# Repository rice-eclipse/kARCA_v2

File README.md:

# kARCA 2.0
kARCA 2.0 is a revision of [kARCA](https://github.com/rice-eclipse/karca):  Rice Eclipse's Engine Control System PCB for the data collection and remote control 
of their Titan II and Proxima Hybrid Rocket Motors

It performs the same functions as kARCA with the addition of thermocouple data collection, driver current monitoring, and battery monitoring.
In addition, various components have been replaced for updated ICs and the power regulation and load cell circuits have been revised.

A detailed description of the changes can be found on  [karca_v2/Docs/changelog](https://github.com/rice-eclipse/kARCA_v2/blob/main/karca_v2/Docs/kARCA_v2_Changelog.csv)

Detailed documentation on the circuit board can be found on [karca_v2/Docs/main_documentation](https://github.com/rice-eclipse/kARCA_v2/tree/main/karca_v2/Docs/karca_v2.md)

## Download and Usage
Download [KiCAD](https://www.kicad.org/download/)

Navigate to your preferred folder and clone into the repository:
```
git clone https://github.com/rice-eclipse/kARCA_v2.git
```
Open KiCAD and open the project file (.kicad_pro):
```
File > Open Project
```

Schematics: [karca_v2/Docs/Schematics](https://github.com/rice-eclipse/kARCA_v2/tree/main/karca_v2/Docs/Schematics)

Spice Simulations: [karca_v2/Docs/Simulations](https://github.com/rice-eclipse/kARCA_v2/tree/main/karca_v2/Docs/Simulations)

Board Files: [karca_v2/Docs/Board_Files](https://github.com/rice-eclipse/kARCA_v2/tree/main/karca_v2/Docs/Board_Files)

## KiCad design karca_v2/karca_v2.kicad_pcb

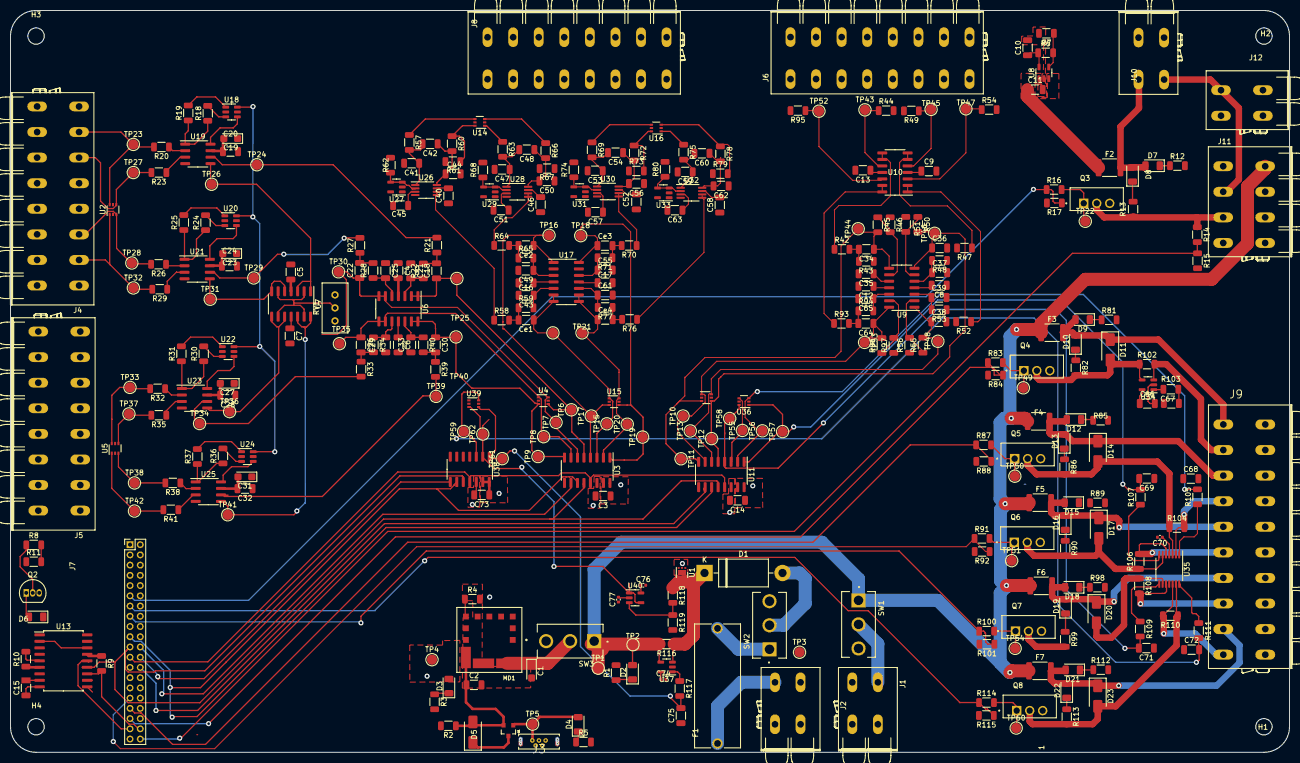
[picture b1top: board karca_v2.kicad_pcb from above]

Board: 4 copper layers, 250.0 x 145.0 mm, 361 parts (0 on the bottom side), 199 nets.

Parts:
C1, C19, C23, C27, C31: 10u; CP_EIA-3216-18_Kemet-A
C2, C10, C11: 10u; C_1206_3216Metric
C3, C4, C5, C6, C7, C16, C17, C20, C24, C28, C32, C40, C42, C45, C46, C48, C51, C52, C54, C57, C58, C60, C63, C66, C67, C68, C69, C71, C72, C73, C75: 0.1u; C_1206_3216Metric
C8, C9, C12, C13, C14: 100n; C_1206_3216Metric
C15: 1u; C_1206_3216Metric
C18, C22, C26, C30, C34, C36, C38, C64: 0.15u; C_1206_3216Metric
C21, C25, C29, C33, C35, C37, C39, C43, C49, C55, C61, C65: 0.075u; C_1206_3216Metric
C41, C44, C47, C50, C53, C56, C59, C62: 0.01u; C_1206_3216Metric
C70, C74, C76, C77: 0.1u; C_0402_1005Metric
Ce1, Ce2, Ce3, Ce4: 0.15u; C_1206_3216Metric
D1: 1N5822RLG; D_DO-201AD_P15.24mm_Horizontal
D2, D3, D4, D7, D8, D9, D10, D12, D13, D15, D16, D18, D19, D21, D22: LED; LED_1206_3216Metric
D5, D11, D14, D17, D20, D23: D_Schottky; D_SMA
D6: HBT; LED_1206_3216Metric
F1: 10A; FUSE_4628
F2, F3, F4, F5, F6, F7: Fuse; Fuse_1812_4532Metric
H1, H2, H3, H4: MountingHole; MountingHole_3.2mm_M3
J1: CON_FAN1; P-2604-1102
J2: Conn_Batt; P-2604-1102
J3: USB_B_Micro; GCT_USB3130-XX-X_REVD
J4: LoadCell_1_2; P-2604-1108
J5: LoadCell_3_4; P-2604-1108
J6, J8: Screw_Terminal_01x08; P-2604-1108
J7: Raspberry_pi; PinHeader_2x20_P2.00mm_Vertical
J9: Screw_Terminal_01x10; P-2604-1110
J10: Keyhole ignition switch; P-2604-1102
J11: Screw_Terminal_01x04; P-2604-1104
J12: Buzzer; P-2604-1102
MD1: OKL-T_6-W12N-C; MURATA_OKL-T-6-W12N-C_0
Q1: AO3401A; SOT23-3
Q2: PN2222A; TO-92_Inline
Q3, Q4, Q5, Q6, Q7, Q8: IRF3708; TO254P1041X444X1930-3
R1: 470; R_1206_3216Metric
R2, R9, R10, R11, R17, R84, R88, R92, R101, R115: 10k; R_1206_3216Metric
R3, R5: 250; R_1206_3216Metric
R4: 1.34k; R_1206_3216Metric
R6: 10.4M; R_1206_3216Metric
R7: 1.2M; R_1206_3216Metric
R8, R12, R13, R16, R20, R21, R22, R23, R26, R27, R28, R29, R32, R33, R34, R35, R38, R39, R40, R41, R42, R43, R47, R48, R52, R53, R58, R59, R62, R64, R65, R68, R70, R71, R74, R76, R77, R80, R81, R82, R83, R85, R86, R87, R89, R90, R91, R93, R94, R98, R99, R100, R103, R105, R107, R109, R111, R112, R113, R114, R117: 1k; R_1206_3216Metric
R14: 15k; R_1206_3216Metric
R15: 5k; R_1206_3216Metric
R18, R24, R30, R36: 330; R_1206_3216Metric
R19, R25, R31, R37, R46, R51, R56, R97: 6.7k; R_1206_3216Metric
R44, R49, R54, R95: 30; R_1206_3216Metric
R45, R50, R55, R96: 47k; R_1206_3216Metric
R57, R60, R63, R66, R69, R72, R75, R78: 100; R_1206_3216Metric
R61, R67, R73, R79: 1M; R_1206_3216Metric
R102, R104, R106, R108, R110, R116: 10m; R_1206_3216Metric
R118: 100k; R_1206_3216Metric
R119: 50k; R_1206_3216Metric
RV1: 30k; Potentiometer_Bourns_3296W_Vertical
SW1, SW2, SW3: SW_SPST; SW_500SSP1S2M2QEA
TP1, TP2, TP3, TP4, TP5, TP6, TP7, TP8, TP9, TP10, TP11, TP12, TP13, TP14, TP15, TP16, TP17, TP18, TP19, TP20, TP21, TP22, TP23, TP24, TP25, TP26, TP27, TP28, TP29, TP30, TP31, TP32, TP33, TP34, TP35, TP36, TP37, TP38, TP39, TP40, TP41, TP42, TP43, TP44, TP45, TP46, TP47, TP48, TP49, TP50, TP51, TP52, TP53, TP54, TP55, TP56, TP57, TP58, TP59, TP60, TP61, TP62: TestPoint; TestPoint_Pad_D2.0mm
U1: TVS1400DRV; WSON-6-1EP_2x2mm_P0.65mm_EP1x1.6mm
U2, U4, U5, U12, U14, U15, U16, U36, U39: NUP4202; SOT-363_SC-70-6
U3, U11: MCP3208; SOIC-16_3.9x9.9mm_P1.27mm
U6, U7, U9, U10, U17: TLV9304xD; SO-14_3.9x8.65mm_P1.27mm
U8: TPS7A24; SOT-23-5
U13: M41T93; SOIC-18W_7.5x11.6mm_P1.27mm
U18, U20, U22, U24: TS5A3159ADBVR; SOT-23-6
U19, U21, U23, U25: AD8223; SOIC-8_3.9x4.9mm_P1.27mm
U26, U28, U30, U32: AD8495; MSOP-8_3x3mm_P0.65mm
U27, U29, U31, U33: SOT-23-5
U34: INA180A4; SOT-23-5
U35: TSSOP-14_4.4x5mm_P0.65mm
U37: INA180A2; SOT-23-5
U38: MCP3204; SO-14_3.9x8.65mm_P1.27mm
U40: TLV9301xDBV; SOT-23-5

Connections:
+5V: C2.1, C3.1, C4.2, C5.2, C8.2, C9.1, C14.1, C16.2, C19.2, C20.2, C23.2, C24.2, C27.2, C28.2, C31.2, C32.2, C40.2, C46.2, C52.2, C58.2, C66.1, C70.1, C73.1, C74.1, C76.1, D3.2 (A), D5.1 (K), D5.2 (A), J4.1, J4.5, J7.2, J7.4, MD1.4 (VOUT), Q1.2 (G), Q1.3 (S), Q2.3 (C), R2.1, R9.1, R10.1, R62.2, R68.2, R74.2, R80.2, RV1.3, TP4.1, U2.5, U3.15 (Vref), U3.16 (Vdd), U4.5, U5.5, U6.4 (V+), U7.4 (V+), U9.4 (V+), U10.4 (V+), U11.15 (Vref), U11.16 (Vdd), U12.5, U13.6 (DU), U13.15 (VCC), U14.5, U15.5, U16.5, U17.4 (V+), U18.5 (V+), U19.7 (Vs+), U20.5 (V+), U21.7 (Vs+), U22.5 (V+), U23.7 (Vs+), U24.5 (V+), U25.7 (Vs+), U26.7 (+Vs), U28.7 (+Vs), U30.7 (+Vs), U32.7 (+Vs), U34.5 (V+), U35.4 (VS), U36.5, U37.5 (V+), U38.13 (Vref), U38.14 (Vdd), U39.5, U40.5 (V+)
+12V: C11.1, D2.2 (A), F2.1, F3.1, F4.1, F5.1, F6.1, F7.1, J11.1, R116.2, SW1.1 (A), SW3.1 (A), TP1.1, TP2.1, U8.1 (IN), U8.3 (EN), U37.4 (-)
/DRV1_ADC: C67.2, R103.2, TP55.1, U11.3 (CH2), U36.4
/DRV2_ADC: C68.2, R105.2, TP56.1, U11.2 (CH1), U36.3
/DRV3_ADC: C69.2, R107.2, TP57.1, U11.1 (CH0), U36.1
/DRV4_ADC: C71.2, R109.2, TP58.1, U11.4 (CH3), U36.6
/Drivers/DRV1_CTL: J7.35, R83.1, R84.1
/Drivers/DRV1_NEG: J9.2, R102.2, U34.3 (+)
/Drivers/DRV2_CTL: J7.33, R87.1, R88.1
/Drivers/DRV2_NEG: J9.4, R104.2, U35.2 (IN1+)
/Drivers/DRV3_CTL: J7.31, R91.1, R92.1
/Drivers/DRV3_NEG: J9.6, R106.2, U35.5 (IN2+)
/Drivers/DRV4_CTL: J7.15, R100.1, R101.1
/Drivers/DRV4_NEG: J9.8, R108.2, U35.10 (IN3+)
/Drivers/DRV5_ADC: C72.2, R111.2, TP59.1, U38.3 (CH2), U39.6
/Drivers/DRV5_CTL: J7.13, R114.1, R115.1
/Drivers/DRV5_NEG: J9.10, R110.2, U35.12 (IN4+)
/Drivers/IGN_CONT: J7.40, R14.2, R15.1
/Drivers/IGN_CTL: J7.11, R16.1, R17.1
/Drivers/IGN_NEG: J11.3, Q3.2 (D), R13.2, R14.1
/Drivers/IGN_POS: D7.2 (A), D8.2 (A), F2.2, J10.1, J10.2, J11.2, J12.1
/Drivers/MOS1: D11.2 (A), Q4.2 (D), R82.2, R102.1, U34.4 (-)
/Drivers/MOS2: D14.2 (A), Q5.2 (D), R86.2, R104.1, U35.3 (IN1-)
/Drivers/MOS3: D17.2 (A), Q6.2 (D), R90.2, R106.1, U35.6 (IN2-)
/Drivers/MOS4: D20.2 (A), Q7.2 (D), R99.2, R108.1, U35.9 (IN3-)
/Drivers/MOS5: D23.2 (A), Q8.2 (D), R110.1, R113.2, U35.13 (IN4-)
/Drivers/driver_nmos1/DRV_POS: D12.2 (A), D13.2 (A), D14.1 (K), F4.2, J9.3
/Drivers/driver_nmos2/DRV_POS: D15.2 (A), D16.2 (A), D17.1 (K), F5.2, J9.5
/Drivers/driver_nmos3/DRV_POS: D18.2 (A), D19.2 (A), D20.1 (K), F6.2, J9.7
/Drivers/driver_nmos4/DRV_POS: D21.2 (A), D22.2 (A), D23.1 (K), F7.2, J9.9
/Drivers/driver_nmos/DRV_POS: D9.2 (A), D10.2 (A), D11.1 (K), F3.2, J9.1
/Load Cells/IN_AMP_VREF: RV1.2, U7.2 (-), U7.6 (-), U7.9 (-), U7.13 (-)
/Load Cells/LC_Amplification1/IN1: J4.6, R26.2, TP28.1, U2.3
/Load Cells/LC_Amplification1/IN2: J4.7, R29.2, TP32.1, U2.1
/Load Cells/LC_Amplification1/OUT: C22.1, TP7.1, TP30.1, U3.6 (CH5), U4.6, U6.6 (-), U6.7
/Load Cells/LC_Amplification2/IN1: R32.2, TP33.1, U5.6
/Load Cells/LC_Amplification2/IN2: R35.2, TP37.1, U5.4
/Load Cells/LC_Amplification2/OUT: C26.1, TP8.1, TP35.1, U3.7 (CH6), U4.1, U6.8, U6.9 (-)
/Load Cells/LC_Amplification3/IN1: R38.2, TP38.1, U5.3
/Load Cells/LC_Amplification3/IN2: R41.2, TP42.1, U5.1
/Load Cells/LC_Amplification3/OUT: C30.1, TP9.1, TP40.1, U3.8 (CH7), U4.3, U6.13 (-), U6.14
/Load Cells/LC_Amplification/IN1: J4.2, R20.2, TP23.1, U2.6
/Load Cells/LC_Amplification/IN2: J4.3, R23.2, TP27.1, U2.4
/Load Cells/LC_Amplification/OUT: C18.1, TP6.1, TP25.1, U3.5 (CH4), U4.4, U6.1, U6.2 (-)
/Load Cells/LC_CS: J7.22, U3.10 (~CS/SHDN)
/Load Cells/LC_SELECTOR: J7.16, U18.6, U20.6, U22.6, U24.6
/Load Cells/TC_1_ADC: Ce1.1, TP14.1, TP15.1, U3.3 (CH2), U15.1, U17.6 (-), U17.7
/Load Cells/TC_2_ADC: Ce2.1, TP16.1, TP17.1, U3.4 (CH3), U15.3, U17.1, U17.2 (-)
/Load Cells/TC_3_ADC: Ce3.1, TP18.1, TP19.1, U3.1 (CH0), U15.4, U17.13 (-), U17.14
/Load Cells/TC_4_ADC: Ce4.1, TP20.1, TP21.1, U3.2 (CH1), U15.6, U17.8, U17.9 (-)
/Pressure Transducers/CS: J7.26, U11.10 (~CS/SHDN)
/Pressure Transducers/pt_circuitry1/IN: R44.1, TP43.1, U10.10 (+)
/Pressure Transducers/pt_circuitry1/OUT: C34.1, R45.2, TP11.1, TP44.1, U9.8, U11.8 (CH7), U12.3
/Pressure Transducers/pt_circuitry2/IN: R49.1, TP45.1, U10.5 (+)
/Pressure Transducers/pt_circuitry2/OUT: C36.1, R50.2, TP12.1, TP46.1, U9.7, U11.5 (CH4), U12.4
/Pressure Transducers/pt_circuitry3/IN: R54.1, TP47.1, U10.3 (+)
/Pressure Transducers/pt_circuitry3/OUT: C38.1, R55.2, TP13.1, TP48.1, U9.1, U11.6 (CH5), U12.6
/Pressure Transducers/pt_circuitry/IN: R95.1, TP52.1, U10.12 (+)
/Pressure Transducers/pt_circuitry/OUT: C64.1, R96.2, TP10.1, TP53.1, U9.14, U11.7 (CH6), U12.1
/Raspberry Pi/ADC2_CS: J7.24, U38.8 (~CS/SHDN)
/Raspberry Pi/RTC_CS: J7.37, U13.14 (E)
/Raspberry Pi/RTC_IRQ: J7.38, R9.2, U13.12 (IRQ)
/Regulators/battery_monitoring/Battery+: D1.1 (K), R116.1, R118.1, U1.4 (IN), U1.5 (IN), U1.6 (IN), U37.3 (+)
/SPI.CLK: J7.23, U3.13 (CLK), U11.13 (CLK), U13.11 (SCL), U38.11 (CLK)
/SPI.MISO: J7.21, U3.12 (Dout), U11.12 (Dout), U13.13 (SDO), U38.10 (Dout)
/SPI.MOSI: J7.19, U3.11 (Din), U11.11 (Din), U13.10 (SDI), U38.9 (Din)
/thermocouples/thermocouple_amp1/IN_1: R63.1, U14.1
/thermocouples/thermocouple_amp1/IN_2: R66.1, R67.2, U14.3
/thermocouples/thermocouple_amp2/IN_1: R69.1, U16.4
/thermocouples/thermocouple_amp2/IN_2: R72.1, R73.2, U16.6
/thermocouples/thermocouple_amp3/IN_1: R75.1, U16.1
/thermocouples/thermocouple_amp3/IN_2: R78.1, R79.2, U16.3
/thermocouples/thermocouple_amp/IN_1: R57.1, U14.4
/thermocouples/thermocouple_amp/IN_2: R60.1, R61.2, U14.6
GND: C1.2, C2.2, C3.2, C4.1, C5.1, C6.1, C6.2, C7.1, C7.2, C8.1, C9.2, C10.2, C11.2, C12.1, C12.2, C13.1, C13.2, C14.2, C15.1, C16.1, C17.1, C17.2, C19.1, C20.1, C21.1, C23.1, C24.1, C25.1, C27.1, C28.1, C29.1, C31.1, C32.1, C33.1, C35.2, C37.2, C39.2, C40.1, C41.2, C43.2, C44.1, C45.1, C45.2, C46.1, C47.2, C49.2, C50.1, C51.1, C51.2, C52.1, C53.2, C55.2, C56.1, C57.1, C57.2, C58.1, C59.2, C61.2, C62.1, C63.1, C63.2, C65.2, C66.2, C67.1, C68.1, C69.1, C70.2, C71.1, C72.1, C73.2, C74.2, C75.1, C76.2, C77.1, C77.2, D6.1 (K), J1.2, J2.1, J3.5 (GND), J3.6 (Shield), J4.4, J4.8, J7.6, J7.9, J7.14, J7.25, J7.30, J7.34, J7.39, J11.4, J12.2, MD1.3 (1_GROUND), MD1.7 (2_GROUND), Q3.3 (S), Q4.3 (S), Q5.3 (S), Q6.3 (S), Q7.3 (S), Q8.3 (S), R1.2, R2.2, R3.2, R4.2, R5.2, R7.2, R11.1, R12.2, R15.2, R17.2, R44.2, R46.1, R49.2, R51.1, R54.2, R56.1, R61.1, R67.1, R73.1, R79.1, R81.2, R84.2, R85.2, R88.2, R89.2, R92.2, R95.2, R97.1, R98.2, R101.2, R112.2, R115.2, R119.2, RV1.1, TP3.1, U1.1 (GND), U1.2 (GND), U1.3 (GND), U1.7 (GND), U2.2, U3.9 (DGND), U3.14 (AGND), U4.2, U5.2, U6.11 (V-), U7.11 (V-), U8.2 (GND), U9.11 (V-), U10.11 (V-), U11.9 (DGND), U11.14 (AGND), U12.2, U13.2 (NF), U13.9 (VSS), U13.16 (NF), U14.2, U15.2, U16.2, U17.11 (V-), U18.2 (GND), U19.4 (-Vs), U20.2 (GND), U21.4 (-Vs), U22.2 (GND), U23.4 (-Vs), U24.2 (GND), U25.4 (-Vs), U26.3 (-Vs), U27.5 (A), U28.3 (-Vs), U29.5 (A), U30.3 (-Vs), U31.5 (A), U32.3 (-Vs), U33.5 (A), U34.2 (GND), U35.11 (GND), U36.2, U37.2 (GND), U38.7 (DGND), U38.12 (AGND), U39.2, U40.2 (V-)
unnamed: C18.2, R21.1, R22.2
unnamed: C22.2, R27.1, R28.2
unnamed: C26.2, R33.1, R34.2
unnamed: C30.2, R39.1, R40.2
unnamed: C34.2, R42.2, R43.1
unnamed: C36.2, R47.2, R48.1
unnamed: C38.2, R52.2, R53.1
unnamed: C64.2, R93.2, R94.1
unnamed: Ce1.2, R58.2, R59.1
unnamed: Ce2.2, R64.2, R65.1
unnamed: Ce3.2, R70.2, R71.1
unnamed: Ce4.2, R76.2, R77.1
unnamed: D1.2 (A), SW2.2 (B)
unnamed: D2.1 (K), R1.1
unnamed: D3.1 (K), R3.1
unnamed: D4.2 (A), J3.1 (VBUS), Q1.1 (D), TP5.1
unnamed: D4.1 (K), R5.1
unnamed: D6.2 (A), Q2.1 (E)
unnamed: D7.1 (K), R12.1
unnamed: D8.1 (K), R13.1
unnamed: D9.1 (K), R81.1
unnamed: D10.1 (K), R82.1
unnamed: D12.1 (K), R85.1
unnamed: D13.1 (K), R86.1
unnamed: D15.1 (K), R89.1
unnamed: D16.1 (K), R90.1
unnamed: D18.1 (K), R98.1
unnamed: D19.1 (K), R99.1
unnamed: D21.1 (K), R112.1
unnamed: D22.1 (K), R113.1
unnamed: J1.1, SW1.2 (B)
unnamed: F1.1, J2.2
unnamed: C10.1, R6.1, U8.5 (OUT)
unnamed: J7.3, R8.2, R11.2
unnamed: MD1.6 (TRIM), R4.1
unnamed: C1.1, MD1.2 (VIN), SW3.2 (B)
unnamed: Q2.2 (B), R8.1
unnamed: Q3.1 (G), R16.2, TP22.1
unnamed: Q4.1 (G), R83.2, TP49.1
unnamed: Q5.1 (G), R87.2, TP50.1
unnamed: Q6.1 (G), R91.2, TP51.1
unnamed: Q7.1 (G), R100.2, TP54.1
unnamed: Q8.1 (G), R114.2, TP60.1
unnamed: R18.2, U18.3
unnamed: R19.2, U18.1
unnamed: R24.2, U20.3
unnamed: R25.2, U20.1
unnamed: R30.2, U22.3
unnamed: R31.2, U22.1
unnamed: R36.2, U24.3
unnamed: R37.2, U24.1
unnamed: R103.1, U34.1
unnamed: R117.1, U37.1
unnamed: F1.2, SW2.1 (A)
unnamed: C21.2, R22.1, U6.3 (+)
unnamed: C25.2, R28.1, U6.5 (+)
unnamed: C29.2, R34.1, U6.10 (+)
unnamed: C33.2, R40.1, U6.12 (+)
unnamed: R6.2, R7.1, U8.4 (FB)
unnamed: C39.1, R53.2, U9.3 (+)
unnamed: R55.1, R56.2, U9.2 (-)
unnamed: C37.1, R48.2, U9.5 (+)
unnamed: R50.1, R51.2, U9.6 (-)
unnamed: C35.1, R43.2, U9.10 (+)
unnamed: R45.1, R46.2, U9.9 (-)
unnamed: C65.1, R94.2, U9.12 (+)
unnamed: R96.1, R97.2, U9.13 (-)
unnamed: R52.1, U10.1, U10.2 (-)
unnamed: R47.1, U10.6 (-), U10.7
unnamed: R42.1, U10.8, U10.9 (-)
unnamed: R93.1, U10.13 (-), U10.14
unnamed: R10.2, U13.5 (RST)
unnamed: C15.2, U13.8 (VBAT)
unnamed: C49.1, R65.2, U17.3 (+)
unnamed: C43.1, R59.2, U17.5 (+)
unnamed: C61.1, R77.2, U17.10 (+)
unnamed: C55.1, R71.2, U17.12 (+)
unnamed: R23.1, U19.3 (+IN)
unnamed: U18.4, U19.8 (+RG)
unnamed: R20.1, U19.2 (-IN)
unnamed: R21.2, TP24.1, U19.6 (OUT)
unnamed: TP26.1, U7.1, U7.3 (+), U19.5 (REF)
unnamed: R18.1, R19.1, U19.1 (Rg)
unnamed: R29.1, U21.3 (+IN)
unnamed: U20.4, U21.8 (+RG)
unnamed: R26.1, U21.2 (-IN)
unnamed: R27.2, TP29.1, U21.6 (OUT)
unnamed: TP31.1, U7.5 (+), U7.7, U21.5 (REF)
unnamed: R24.1, R25.1, U21.1 (Rg)
unnamed: R35.1, U23.3 (+IN)
unnamed: U22.4, U23.8 (+RG)
unnamed: R32.1, U23.2 (-IN)
unnamed: R33.2, TP34.1, U23.6 (OUT)
unnamed: TP36.1, U7.8, U7.10 (+), U23.5 (REF)
unnamed: R30.1, R31.1, U23.1 (Rg)
unnamed: R41.1, U25.3 (+IN)
unnamed: U24.4, U25.8 (+RG)
unnamed: R38.1, U25.2 (-IN)
unnamed: R39.2, TP39.1, U25.6 (OUT)
unnamed: TP41.1, U7.12 (+), U7.14, U25.5 (REF)
unnamed: R36.1, R37.1, U25.1 (Rg)
unnamed: C42.1, C44.2, R60.2, U26.8 (+IN)
unnamed: C41.1, C42.2, R57.2, U26.1 (-IN)
unnamed: R62.1, U26.2 (REF), U27.3 (C), U27.4 (REF)
unnamed: R58.1, U26.5 (SENSE), U26.6
unnamed: C48.1, C50.2, R66.2, U28.8 (+IN)
unnamed: C47.1, C48.2, R63.2, U28.1 (-IN)
unnamed: R68.1, U28.2 (REF), U29.3 (C), U29.4 (REF)
unnamed: R64.1, U28.5 (SENSE), U28.6
unnamed: C54.1, C56.2, R72.2, U30.8 (+IN)
unnamed: C53.1, C54.2, R69.2, U30.1 (-IN)
unnamed: R74.1, U30.2 (REF), U31.3 (C), U31.4 (REF)
unnamed: R70.1, U30.5 (SENSE), U30.6
unnamed: C60.1, C62.2, R78.2, U32.8 (+IN)
unnamed: C59.1, C60.2, R75.2, U32.1 (-IN)
unnamed: R80.1, U32.2 (REF), U33.3 (C), U33.4 (REF)
unnamed: R76.1, U32.5 (SENSE), U32.6
unnamed: R105.1, U35.1 (OUT1)
unnamed: R107.1, U35.7 (OUT2)
unnamed: R109.1, U35.8 (OUT3)
unnamed: R111.1, U35.14 (OUT4)
unnamed: C75.2, R117.2, TP61.1, U38.1 (CH0), U39.4
unnamed: TP62.1, U38.2 (CH1), U39.3, U40.1, U40.4 (-)
unnamed: R118.2, R119.1, U40.3 (+)

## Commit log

2024-09-29 initial
2024-09-30 modified sch
2024-11-15 Version alpha
2024-11-15 unrouted adc traces
2024-11-18 fkkkkkkkkkk
2024-11-18 quick fix
2024-11-18 Checkpoint before ripping everything apart
2024-11-19 ripping it all
2024-11-19 Saved the 12V rail
2024-11-19 rearrange regs
2024-11-20 discrete traces
2024-11-21 fixed TVS Diodes
2024-11-23 vias pt 1
2024-11-23 vias pt 2
2024-11-23 fixed violations
2024-11-23 passed DRC
2024-11-23 passed DRC fr
2024-11-23 stitching capacitors for SPI signals
2024-11-27 Fixed ground capacitors
2024-11-27 Fixed silkscreen
2024-11-29 save before rerouting
2024-12-01 pin 1 labels and straight traces to IC pads
2024-12-01 fixed pmos
2024-12-02 replaced digital switches with jumpers, simpler design
2024-12-03 Passed all DRC, Added safety jumper to isolate regulators from rest of the board
2024-12-05 last:
2024-12-15 changed capacitor values and sizes for production
2024-12-27 cleaned up documentation. Added production files and BOM. Marked Thermocouple components and THT components as DNP (excluded them from BOM too) to match version sent to JLCPCB for fabrication
2024-12-27 main documentation
2024-12-28 added changelog
2024-12-28 added Spice simulation files
2024-12-28 added board files
2025-01-04 BOM of THT added
2025-01-24 updated THT BOM
2025-05-25 revisions for V2.1
2025-05-25 added production files
2025-05-25 updated BOM
2025-05-25 updated POS
2025-06-17 saving changes
2025-06-17 started detailed docs
2025-06-17 finished first draft of docs
2025-06-17 cropped images
2025-06-17 fixed typos
2025-09-20 Replaced header with a smaller one, added silksreen labels, and removed secondary USB power source
2025-09-23 changed pin header to a smaller one and removed USB secondary power supply
2025-12-04 new design: chip on board
2026-03-21 re-added sims and gerbers
2026-03-21 added gitignore to remvoe backups
2026-03-23 removing zip files
2026-03-23 reorganized ADCs
2026-03-24 finished schematic for v2.1
2026-03-25 restart: way too many changes made
2026-03-25 swapped adcs
2026-03-25 added precision shunt reference to ADCs and second SPI bus for driver current and battery voltage monitors
2026-03-25 Swapped IRF3708 FETs for AO3400 for more compact package
2026-03-27 All tests passed. Going to run DFM next
2026-03-28 changed diode to SMD schottky and fixed switches
2026-03-28 removed accidental zip
2026-03-28 fixed all routing. Now need to clean up vias
2026-03-28 via array completed. Time for gerbers and bom
2026-03-29 final production version
2026-05-24 fixed changelog
2026-05-24 removed extraneous files
    updated gitignore to remove extraneous files
    removed unnecessary files
    updated gitignore to remove extraneous files
    removed extra spice sims
    removed all extra files
2026-05-24 updated all images
2026-05-24 Updated docs
